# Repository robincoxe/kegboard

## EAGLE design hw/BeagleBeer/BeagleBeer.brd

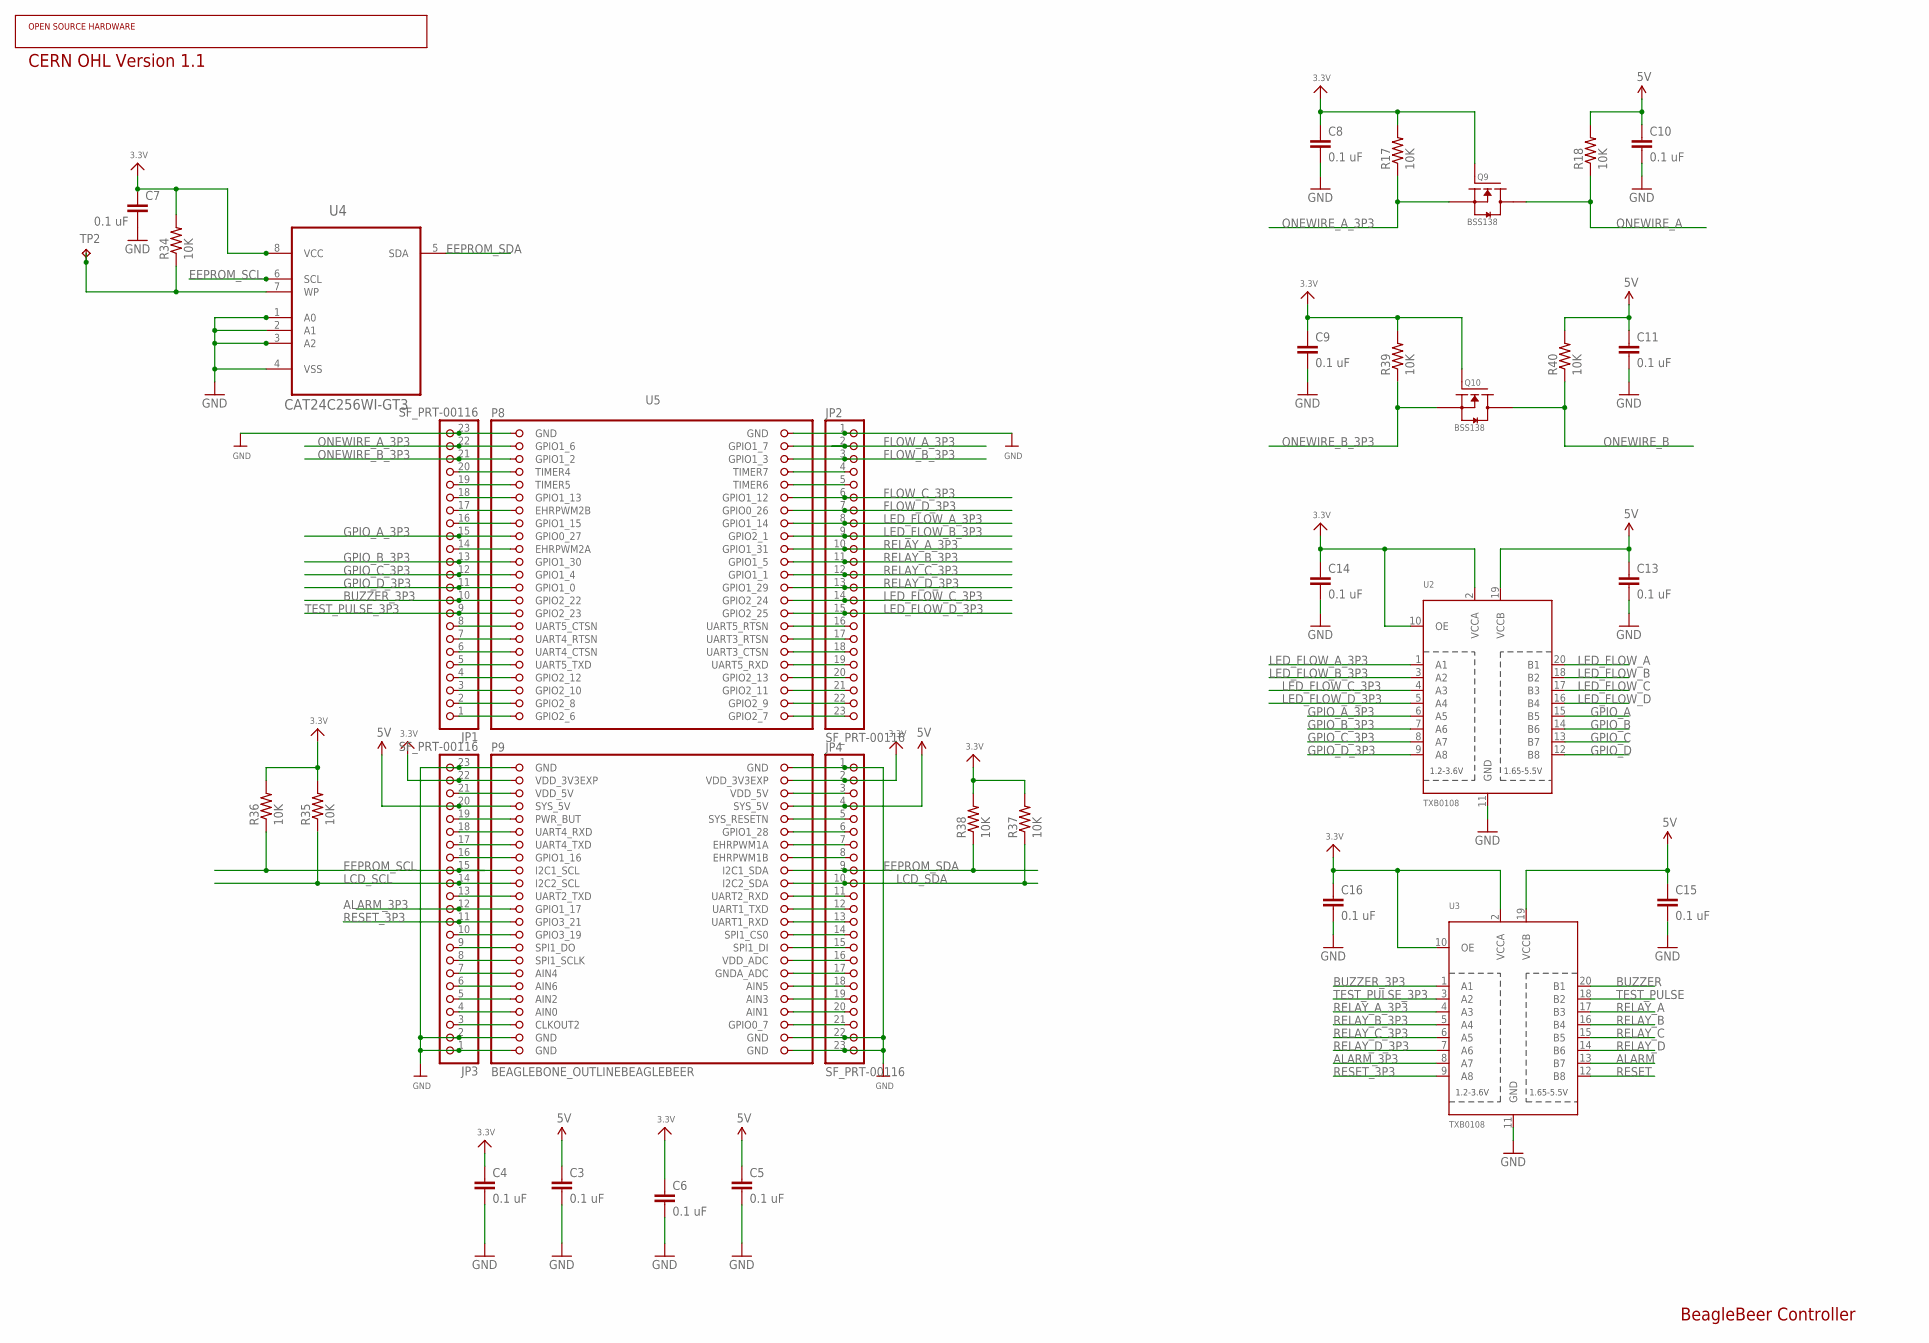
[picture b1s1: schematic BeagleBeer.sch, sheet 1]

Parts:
C3, C4, C5, C6, C7, C8, C9, C10, C11, C13, C14, C15, C16: 0.1 uF; 0805
JP1, JP2, JP3, JP4: SF_PRT-00116; 1X23_ROUND_70MIL
Q9, Q10: BSS138; SOT323
R17, R18, R34, R35, R36, R37, R38, R39, R40: 10K; 0805
TP2: TPTP18SQ; TP18SQ
U2, U3: TXB0108; TSSOP20
U4: CAT24C256WI-GT3; SOIC127P600X175-8N
U5: BEAGLEBONE_OUTLINEBEAGLEBEER; BEAGLEBEER_SHIELD

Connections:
3.3V: C4.1, C6.1, C7.1, C8.1, C9.1, C14.1, C16.1, JP3.22, JP4.2, Q9.1 (G), Q10.1 (G), R17.2, R34.2, R35.2, R36.2, R37.2, R38.2, R39.2, U2.2 (VCCA), U2.10 (OE), U3.2 (VCCA), U3.10 (OE), U4.8 (VCC), U5.49 (VDD_3V3EXP), U5.50 (VDD_3V3EXP); also elsewhere on the board
5V: C3.1, C5.1, C10.1, C11.1, C13.1, C15.1, JP3.20, JP4.4, R18.2, R40.2, U2.19 (VCCB), U3.19 (VCCB), U5.53 (SYS_5V), U5.54 (SYS_5V); also elsewhere on the board
ALARM: U3.13 (B7); also elsewhere on the board
ALARM_3P3: JP3.12, U3.8 (A7), U5.69 (GPIO1_17)
BUZZER: U3.20 (B1); also elsewhere on the board
BUZZER_3P3: JP1.10, U3.1 (A1), U5.27 (GPIO2_22)
EEPROM_SCL: JP3.15, R36.1, U4.6 (SCL), U5.63 (I2C1_SCL)
EEPROM_SDA: JP4.9, R38.1, U4.5 (SDA), U5.64 (I2C1_SDA)
FLOW_A_3P3: JP2.2, U5.4 (GPIO1_7)
FLOW_B_3P3: JP2.3, U5.6 (GPIO1_3)
FLOW_C_3P3: JP2.6, U5.12 (GPIO1_12)
FLOW_D_3P3: JP2.7, U5.14 (GPIO0_26)
GND: C3.2, C4.2, C5.2, C6.2, C7.2, C8.2, C9.2, C10.2, C11.2, C13.2, C14.2, C15.2, C16.2, JP1.23, JP2.1, JP3.1, JP3.2, JP3.23, JP4.1, JP4.22, JP4.23, U2.11 (GND), U3.11 (GND), U4.1 (A0), U4.2 (A1), U4.3 (A2), U4.4 (VSS), U5.1 (GND), U5.2 (GND), U5.47 (GND), U5.48 (GND), U5.89 (GND), U5.90 (GND), U5.91 (GND), U5.92 (GND); also elsewhere on the board
GPIO_A: U2.15 (B5); also elsewhere on the board
GPIO_A_3P3: JP1.15, U2.6 (A5), U5.17 (GPIO0_27)
GPIO_B: U2.14 (B6); also elsewhere on the board
GPIO_B_3P3: JP1.13, U2.7 (A6), U5.21 (GPIO1_30)
GPIO_C: U2.13 (B7); also elsewhere on the board
GPIO_C_3P3: JP1.12, U2.8 (A7), U5.23 (GPIO1_4)
GPIO_D: U2.12 (B8); also elsewhere on the board
GPIO_D_3P3: JP1.11, U2.9 (A8), U5.25 (GPIO1_0)
LCD_SCL: JP3.14, R35.1, U5.65 (I2C2_SCL)
LCD_SDA: JP4.10, R37.1, U5.66 (I2C2_SDA)
LED_FLOW_A: U2.20 (B1); also elsewhere on the board
LED_FLOW_A_3P3: JP2.8, U2.1 (A1), U5.16 (GPIO1_14)
LED_FLOW_B: U2.18 (B2); also elsewhere on the board
LED_FLOW_B_3P3: JP2.9, U2.3 (A2), U5.18 (GPIO2_1)
LED_FLOW_C: U2.17 (B3); also elsewhere on the board
LED_FLOW_C_3P3: JP2.14, U2.4 (A3), U5.28 (GPIO2_24)
LED_FLOW_D: U2.16 (B4); also elsewhere on the board
LED_FLOW_D_3P3: JP2.15, U2.5 (A4), U5.30 (GPIO2_25)
unnamed: JP1.2, U5.43 (GPIO2_8)
unnamed: JP1.1, U5.45 (GPIO2_6)
unnamed: JP1.20, U5.7 (TIMER4)
unnamed: JP1.19, U5.9 (TIMER5)
unnamed: JP2.16, U5.32 (UART5_RTSN)
unnamed: JP1.17, U5.13 (EHRPWM2B)
unnamed: JP2.17, U5.34 (UART3_RTSN)
unnamed: JP2.18, U5.36 (UART3_CTSN)
unnamed: JP1.14, U5.19 (EHRPWM2A)
unnamed: JP2.19, U5.38 (UART5_RXD)
unnamed: JP2.20, U5.40 (GPIO2_13)
unnamed: JP2.21, U5.42 (GPIO2_11)
unnamed: JP2.22, U5.44 (GPIO2_9)
unnamed: JP2.23, U5.46 (GPIO2_7)
unnamed: JP1.8, U5.31 (UART5_CTSN)
unnamed: JP1.7, U5.33 (UART4_RTSN)
unnamed: JP1.6, U5.35 (UART4_CTSN)
unnamed: JP1.5, U5.37 (UART5_TXD)
unnamed: JP1.4, U5.39 (GPIO2_12)
unnamed: JP1.3, U5.41 (GPIO2_10)
unnamed: JP2.4, U5.8 (TIMER7)
unnamed: JP2.5, U5.10 (TIMER6)
unnamed: JP3.21, U5.51 (VDD_5V)
unnamed: JP3.19, U5.55 (PWR_BUT)
unnamed: JP3.18, U5.57 (UART4_RXD)
unnamed: JP3.17, U5.59 (UART4_TXD)
unnamed: JP3.16, U5.61 (GPIO1_16)
unnamed: JP3.13, U5.67 (UART2_TXD)
unnamed: JP3.10, U5.73 (GPIO3_19)
unnamed: JP3.9, U5.75 (SPI1_DO)
unnamed: JP3.8, U5.77 (SPI1_SCLK)
unnamed: JP3.7, U5.79 (AIN4)
unnamed: JP3.6, U5.81 (AIN6)
unnamed: JP3.5, U5.83 (AIN2)
unnamed: JP3.4, U5.85 (AIN0)
unnamed: JP3.3, U5.87 (CLKOUT2)
unnamed: JP4.21, U5.88 (GPIO0_7)
unnamed: JP4.3, U5.52 (VDD_5V)
unnamed: JP4.5, U5.56 (SYS_RESETN)
unnamed: JP4.6, U5.58 (GPIO1_28)
unnamed: JP4.7, U5.60 (EHRPWM1A)
unnamed: JP4.8, U5.62 (EHRPWM1B)
unnamed: JP4.11, U5.68 (UART2_RXD)
unnamed: JP4.12, U5.70 (UART1_TXD)
unnamed: JP4.13, U5.72 (UART1_RXD)
unnamed: JP4.14, U5.74 (SPI1_CS0)
unnamed: JP4.15, U5.76 (SPI1_DI)
unnamed: JP4.16, U5.78 (VDD_ADC)
unnamed: JP4.17, U5.80 (GNDA_ADC)
unnamed: JP4.18, U5.82 (AIN5)
unnamed: JP4.19, U5.84 (AIN3)
unnamed: JP4.20, U5.86 (AIN1)
unnamed: R34.1, TP2.TP, U4.7 (WP)
ONEWIRE_A: Q9.3 (D1), R18.1; also elsewhere on the board
ONEWIRE_A_3P3: JP1.22, Q9.2 (S), R17.1, U5.3 (GPIO1_6)
ONEWIRE_B: Q10.3 (D1), R40.1; also elsewhere on the board
ONEWIRE_B_3P3: JP1.21, Q10.2 (S), R39.1, U5.5 (GPIO1_2)
ONEWIRE_C_3P3: JP1.18, U5.11 (GPIO1_13)
ONEWIRE_D_3P3: JP1.16, U5.15 (GPIO1_15)
RELAY_A: U3.17 (B3); also elsewhere on the board
RELAY_A_3P3: JP2.10, U3.4 (A3), U5.20 (GPIO1_31)
RELAY_B: U3.16 (B4); also elsewhere on the board
RELAY_B_3P3: JP2.11, U3.5 (A4), U5.22 (GPIO1_5)
RELAY_C: U3.15 (B5); also elsewhere on the board
RELAY_C_3P3: JP2.12, U3.6 (A5), U5.24 (GPIO1_1)
RELAY_D: U3.14 (B6); also elsewhere on the board
RELAY_D_3P3: JP2.13, U3.7 (A6), U5.26 (GPIO1_29)
RESET: U3.12 (B8); also elsewhere on the board
RESET_3P3: JP3.11, U3.9 (A8), U5.71 (GPIO3_21)
TEST_PULSE: U3.18 (B2); also elsewhere on the board
TEST_PULSE_3P3: JP1.9, U3.3 (A2), U5.29 (GPIO2_23)

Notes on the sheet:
BeagleBeer Controller

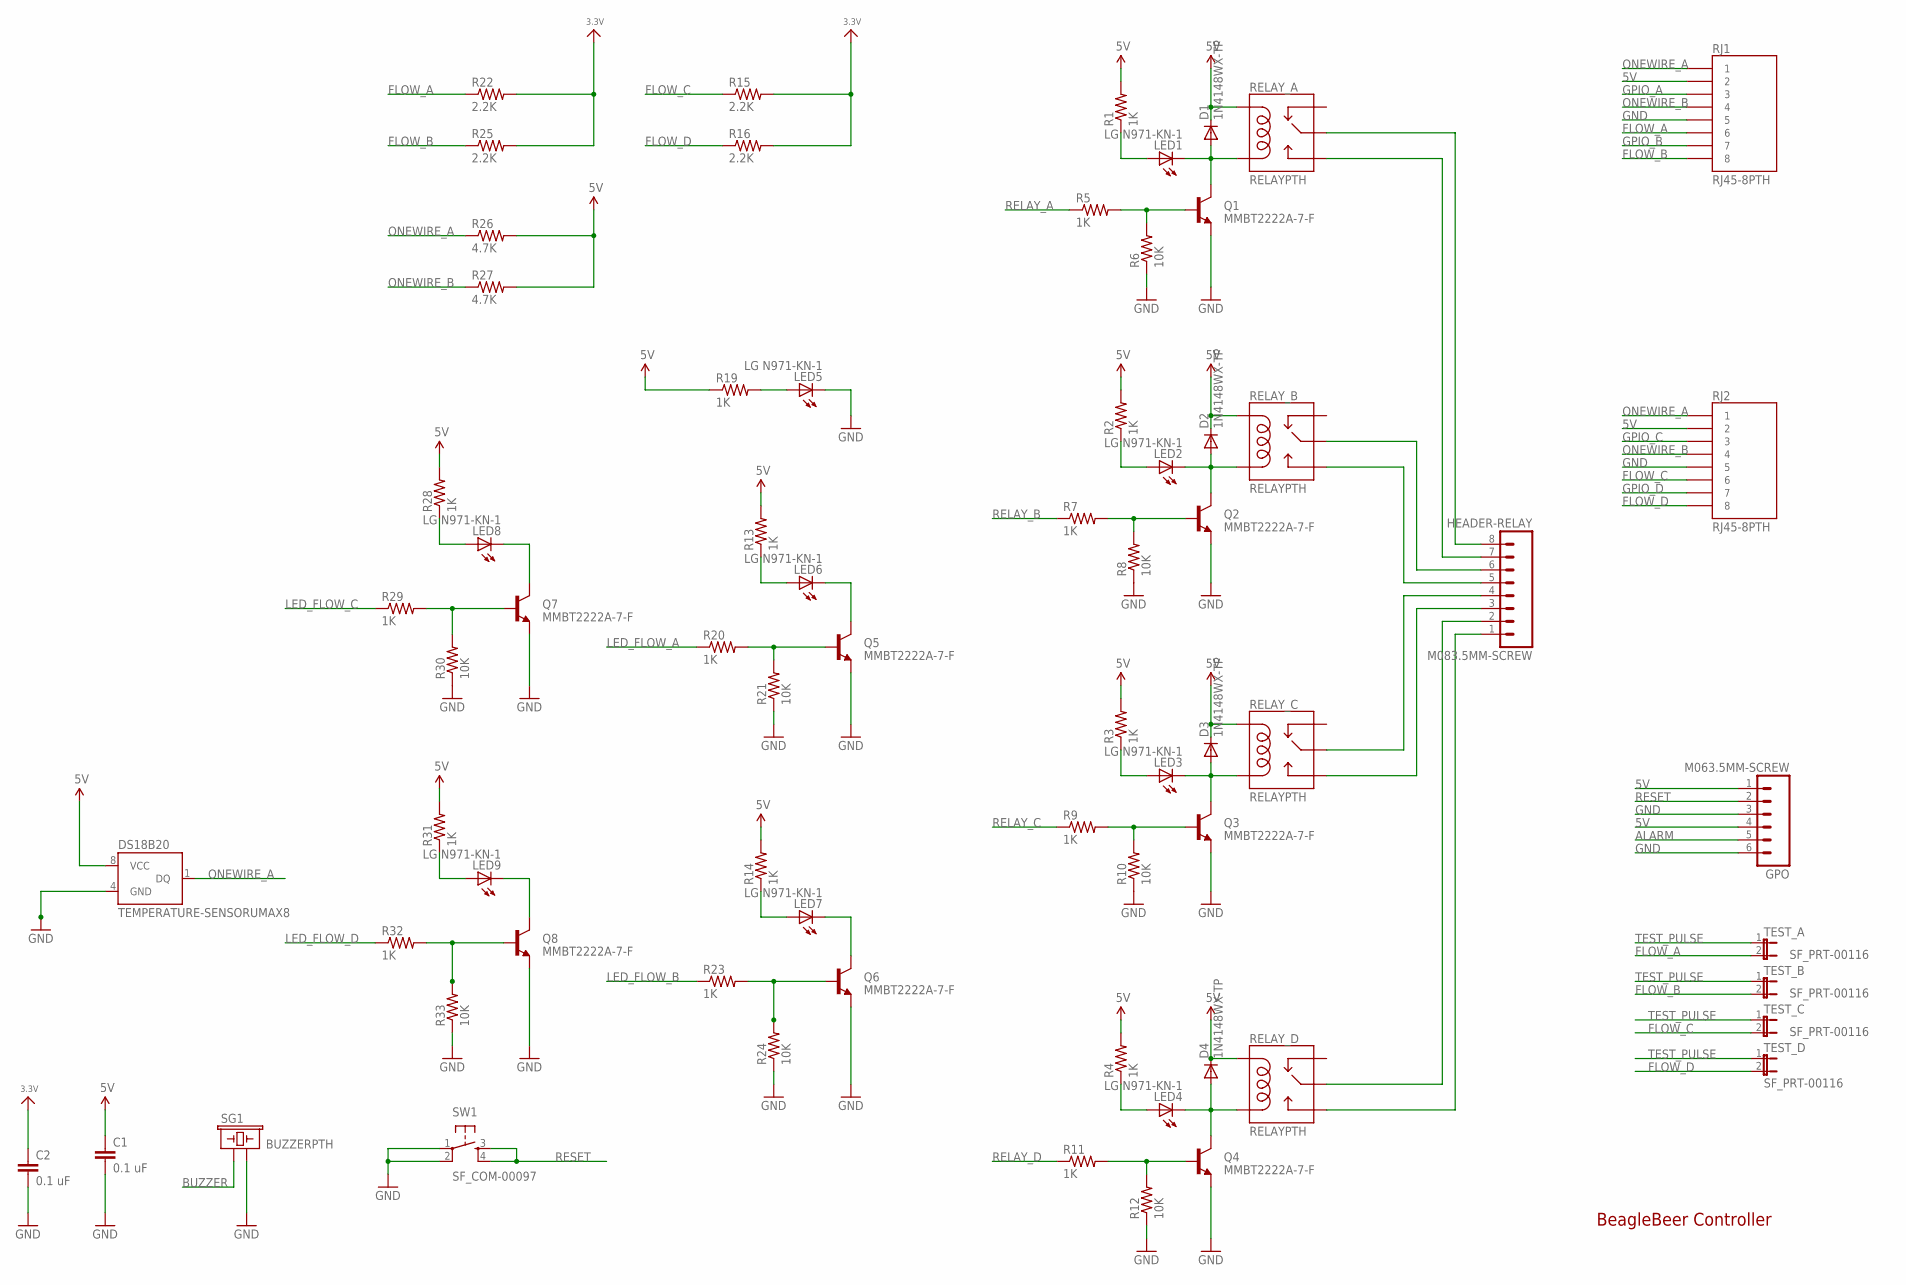
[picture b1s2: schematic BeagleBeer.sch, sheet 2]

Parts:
C1, C2: 0.1 uF; 0805
D1, D2, D3, D4: 1N4148WX-TP; SOD-323
GPO: M063.5MM-SCREW; SCREWTERMINAL-3.5MM-6
HEADER-RELAY: M083.5MM-SCREW; SCREWTERMINAL-3.5MM-8
LED1, LED2, LED3, LED4, LED5, LED6, LED7, LED8, LED9: LG N971-KN-1; LED-1206
Q1, Q2, Q3, Q4, Q5, Q6, Q7, Q8: MMBT2222A-7-F; SOT23-3
R1, R2, R3, R4, R5, R7, R9, R11, R13, R14, R19, R20, R23, R28, R29, R31, R32: 1K; 0805
R6, R8, R10, R12, R21, R24, R30, R33: 10K; 0805
R15, R16, R22, R25: 2.2K; 0805
R26, R27: 4.7K; 0805
RELAY_A: RELAYPTH; RELAY-G5Q
RELAY_B: RELAYPTH; RELAY-G5Q
RELAY_C: RELAYPTH; RELAY-G5Q
RELAY_D: RELAYPTH; RELAY-G5Q
RJ1, RJ2: RJ45-8PTH; RJ45-8
SG1: BUZZERPTH; BUZZER-12MM
SW1: SF_COM-00097; TACTILE-PTH
TEST_A: SF_PRT-00116; 1X02
TEST_B: SF_PRT-00116; 1X02
TEST_C: SF_PRT-00116; 1X02
TEST_D: SF_PRT-00116; 1X02
U1: TEMPERATURE-SENSORUMAX8; UMAX8

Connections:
3.3V: C2.1, R15.2, R16.2, R22.2, R25.2; also elsewhere on the board
5V: C1.1, D1.1 (C), D2.1 (C), D3.1 (C), D4.1 (C), GPO.1, GPO.4, R1.2, R2.2, R3.2, R4.2, R13.2, R14.2, R19.1, R26.2, R27.2, R28.2, R31.2, RELAY_A.5 (COIL1), RELAY_B.5 (COIL1), RELAY_C.5 (COIL1), RELAY_D.5 (COIL1), RJ1.2, RJ2.2, U1.8 (VCC); also elsewhere on the board
ALARM: GPO.5; also elsewhere on the board
BUZZER: SG1.+ (1); also elsewhere on the board
FLOW_A: R22.1, RJ1.6, TEST_A.2
FLOW_B: R25.1, RJ1.8, TEST_B.2
FLOW_C: R15.1, RJ2.6, TEST_C.2
FLOW_D: R16.1, RJ2.8, TEST_D.2
GND: C1.2, C2.2, GPO.3, GPO.6, LED5.C, Q1.2 (E), Q2.2 (E), Q3.2 (E), Q4.2 (E), Q5.2 (E), Q6.2 (E), Q7.2 (E), Q8.2 (E), R6.1, R8.1, R10.1, R12.1, R21.1, R24.1, R30.1, R33.1, RJ1.5, RJ2.5, SG1.- (2), SW1.1, SW1.2, U1.4 (GND); also elsewhere on the board
GPIO_A: RJ1.3; also elsewhere on the board
GPIO_B: RJ1.7; also elsewhere on the board
GPIO_C: RJ2.3; also elsewhere on the board
GPIO_D: RJ2.7; also elsewhere on the board
LED_FLOW_A: R20.1; also elsewhere on the board
LED_FLOW_B: R23.1; also elsewhere on the board
LED_FLOW_C: R29.1; also elsewhere on the board
LED_FLOW_D: R32.1; also elsewhere on the board
unnamed: LED8.C, Q7.3 (C)
unnamed: LED8.A, R28.1
unnamed: Q7.1 (B), R29.2, R30.2
unnamed: LED9.C, Q8.3 (C)
unnamed: D1.2 (A), LED1.C, Q1.3 (C), RELAY_A.1 (COIL2)
unnamed: D2.2 (A), LED2.C, Q2.3 (C), RELAY_B.1 (COIL2)
unnamed: D3.2 (A), LED3.C, Q3.3 (C), RELAY_C.1 (COIL2)
unnamed: D4.2 (A), LED4.C, Q4.3 (C), RELAY_D.1 (COIL2)
unnamed: Q1.1 (B), R5.2, R6.2
unnamed: Q2.1 (B), R7.2, R8.2
unnamed: Q3.1 (B), R9.2, R10.2
unnamed: Q4.1 (B), R11.2, R12.2
unnamed: LED5.A, R19.2
unnamed: HEADER-RELAY.8, RELAY_A.2 (MAIN)
unnamed: HEADER-RELAY.7, RELAY_A.3 (NO)
unnamed: HEADER-RELAY.6, RELAY_B.2 (MAIN)
unnamed: HEADER-RELAY.5, RELAY_B.3 (NO)
unnamed: LED9.A, R31.1
unnamed: Q8.1 (B), R32.2, R33.2
unnamed: HEADER-RELAY.4, RELAY_C.2 (MAIN)
unnamed: HEADER-RELAY.3, RELAY_C.3 (NO)
unnamed: HEADER-RELAY.2, RELAY_D.2 (MAIN)
unnamed: HEADER-RELAY.1, RELAY_D.3 (NO)
unnamed: LED1.A, R1.1
unnamed: LED2.A, R2.1
unnamed: LED3.A, R3.1
unnamed: LED4.A, R4.1
unnamed: LED6.C, Q5.3 (C)
unnamed: LED6.A, R13.1
unnamed: Q5.1 (B), R20.2, R21.2
unnamed: LED7.C, Q6.3 (C)
unnamed: LED7.A, R14.1
unnamed: Q6.1 (B), R23.2, R24.2
ONEWIRE_A: R26.1, RJ1.1, RJ2.1, U1.1 (DQ); also elsewhere on the board
ONEWIRE_B: R27.1, RJ1.4, RJ2.4; also elsewhere on the board
RELAY_A: R5.1; also elsewhere on the board
RELAY_B: R7.1; also elsewhere on the board
RELAY_C: R9.1; also elsewhere on the board
RELAY_D: R11.1; also elsewhere on the board
RESET: GPO.2, SW1.3, SW1.4; also elsewhere on the board
TEST_PULSE: TEST_A.1, TEST_B.1, TEST_C.1, TEST_D.1; also elsewhere on the board

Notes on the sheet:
BeagleBeer Controller

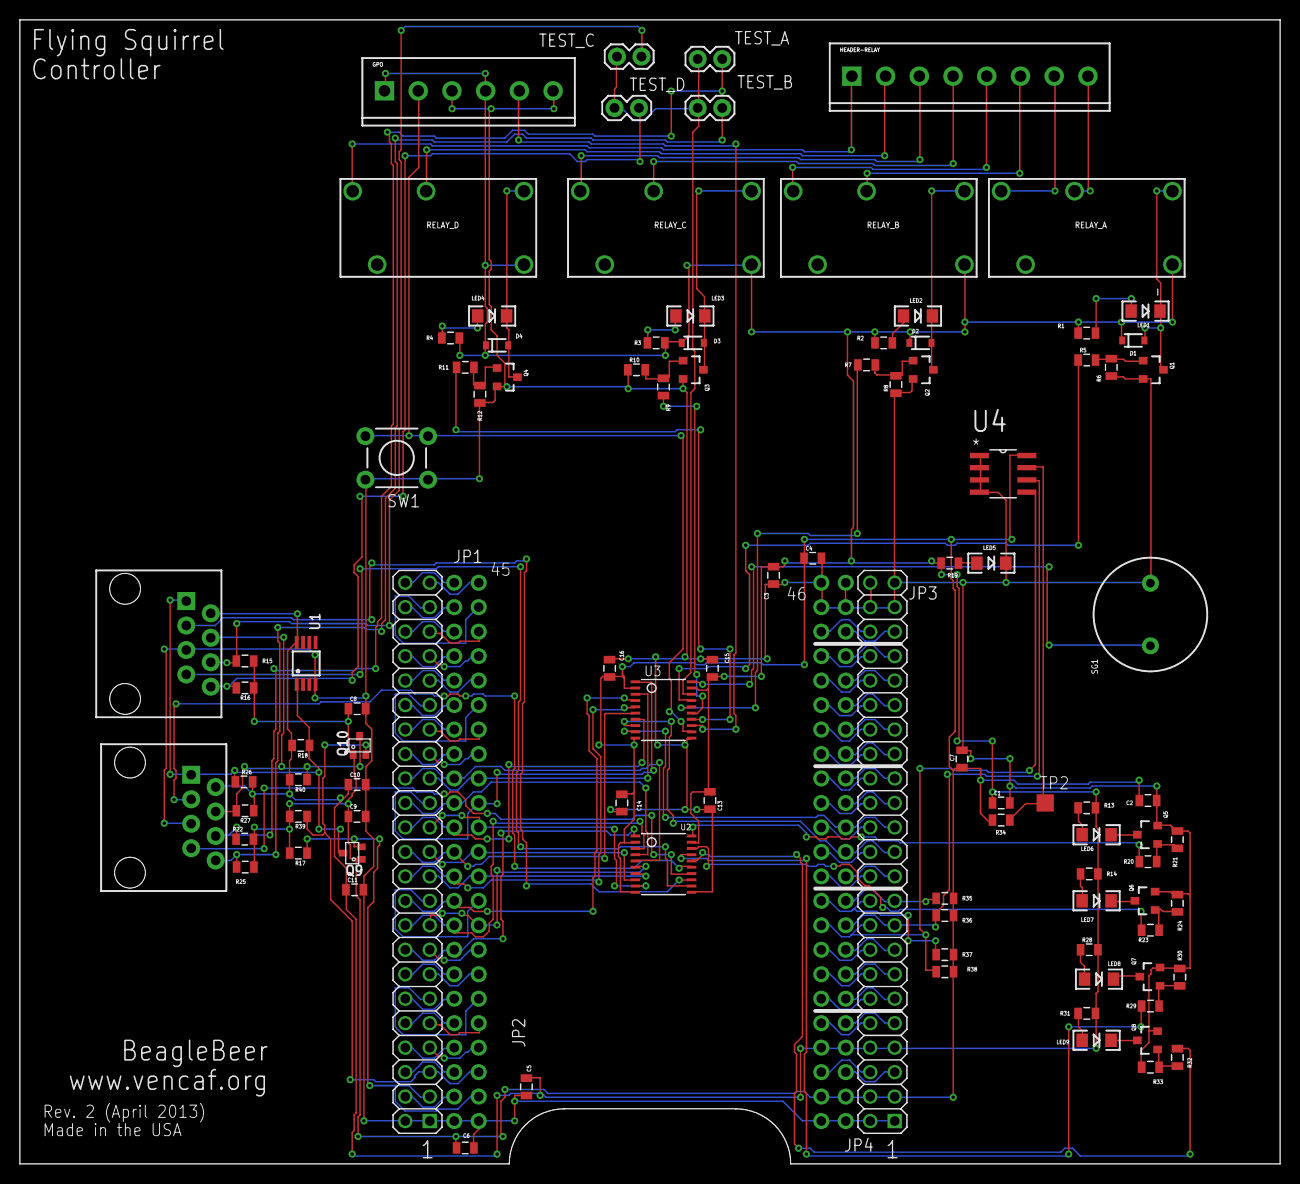
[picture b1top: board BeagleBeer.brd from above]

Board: 2 copper layers, 130.8 x 118.7 mm, 102 parts (0 on the bottom side), 139 nets.

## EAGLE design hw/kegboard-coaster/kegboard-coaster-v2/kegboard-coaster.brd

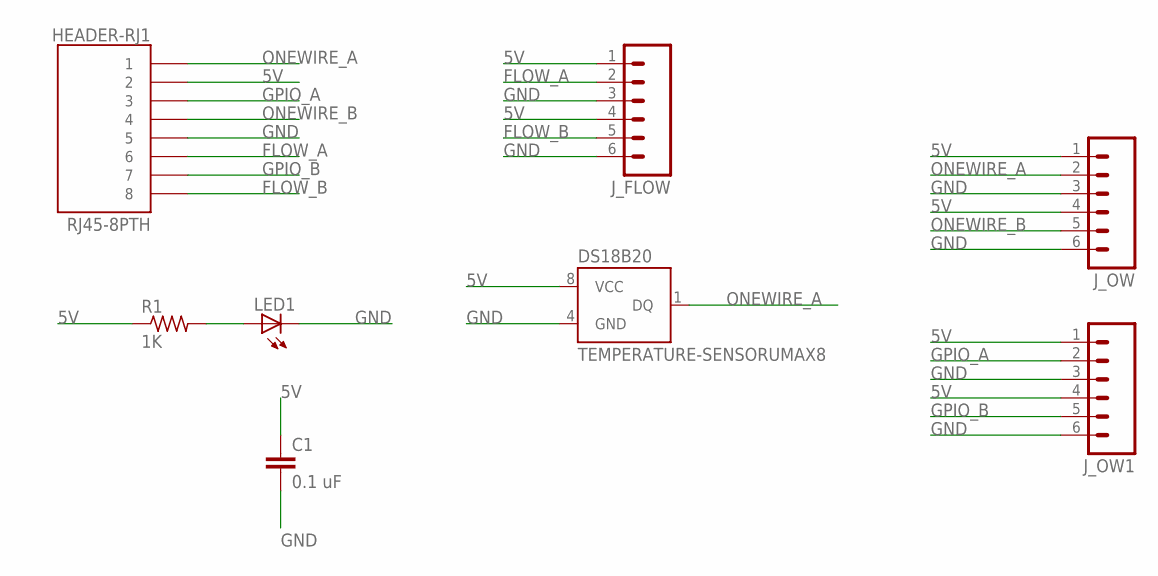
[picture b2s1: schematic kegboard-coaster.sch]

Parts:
C1: 0.1 uF; 0805
HEADER-RJ1: RJ45-8PTH; RJ45-8
J_FLOW: M06SIP; 1X06
J_OW, J_OW1: M06SIP; 1X06
LED1: LED-FKIT-1206; FKIT-LED-1206
R1: 1K; R0805
U$1: TEMPERATURE-SENSORUMAX8; UMAX8

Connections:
5V: C1.1, HEADER-RJ1.2, J_FLOW.1, J_FLOW.4, J_OW.1, J_OW.4, J_OW1.1, J_OW1.4, R1.1, U$1.8 (VCC)
FLOW_A: HEADER-RJ1.6, J_FLOW.2
FLOW_B: HEADER-RJ1.8, J_FLOW.5
GND: C1.2, HEADER-RJ1.5, J_FLOW.3, J_FLOW.6, J_OW.3, J_OW.6, J_OW1.3, J_OW1.6, LED1.C, U$1.4 (GND)
GPIO_A: HEADER-RJ1.3, J_OW1.2
GPIO_B: HEADER-RJ1.7, J_OW1.5
unnamed: LED1.A, R1.2
ONEWIRE_A: HEADER-RJ1.1, J_OW.2, U$1.1 (DQ)
ONEWIRE_B: HEADER-RJ1.4, J_OW.5

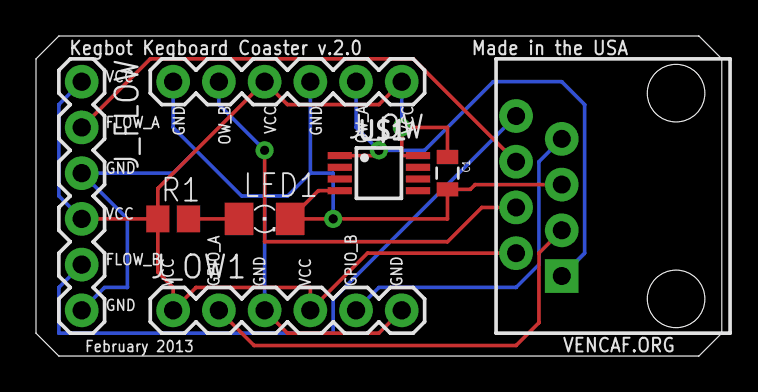
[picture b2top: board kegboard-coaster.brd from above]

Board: 2 copper layers, 38.1 x 17.8 mm, 8 parts (0 on the bottom side), 9 nets.

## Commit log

2013-01-24 Modify Kegbot Kegboard Coaster to use SMD components (0805 R & C, 1206 LED)
2013-01-24 Sync.
2013-01-24 Change folder name to v2.
2013-01-24 Fix .gitignore
2013-01-24 Use Adafruit BeagleBone Proto Board as starting point for BeagleBeer cape.
2013-01-25 Replace Temp Sensor with SMD package
2013-01-25 Update BOM
2013-01-25 Fix temp. sensor REFDES
2013-01-25 Move Gerbers to folder
2013-01-25 Fix Temp Sensor REFDES
2013-01-26 Fix trace between resistor & LED
2013-02-05 Update archive.
2013-02-07 Modify Kegbot Coaster silkscreen
2013-02-07 Modify silkscreen
2013-02-11 Route BeagleBeer Flying Squirrel Controller PCB.
2013-02-11 Controller PCB layout.
2013-02-14 Run ERC on Controller and reroute.
2013-02-14 Rename Gerber folders <project-name>-FAB
2013-02-14 Add board outline to CAM file/Gerber file sets for Sunstone Circuits.
2013-02-14 EPF Mods.
2013-02-14 Clean up Gerber files. Generate XY parts placement files.
2013-02-18 Add misc. SMD datasheets and master BOM.
2013-02-20 Rename master branch venturecafe
2013-03-02 update archive with as built files
2013-03-16 commit changes
2013-04-13 BeagleBeer v2
2013-04-13 BeagleBeer v2 Run ERCs and DRCs
2013-04-13 Remove redundant RJ45 connectors on BeagleBeer
2013-05-08 Commit BeagleBone manual and BeagleBeer Python test script
2013-05-08 Add comments and credits to BeagleBeer Python test script
2014-03-22 Kegboard mini & beaglebeer Python

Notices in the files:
parts and their libraries:
SparkFun-LED: Licensing: CC v3.0 Share-Alike You are welcome to use this library for commercial purposes.
dframes: CERN OHL Version 1.1
